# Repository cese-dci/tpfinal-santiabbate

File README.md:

# TP final de la materia Diseño de Circuitos Impresos - CESE - 2020A
## Réplica  modificada Heltec Wifi LoRA V2

Propuesta general: Eliminar el display OLED y reemplazar los circuitos integrados ESP32 y SX1278 por los módulos ESP32-WROOM y Ra-01.

## Resultado

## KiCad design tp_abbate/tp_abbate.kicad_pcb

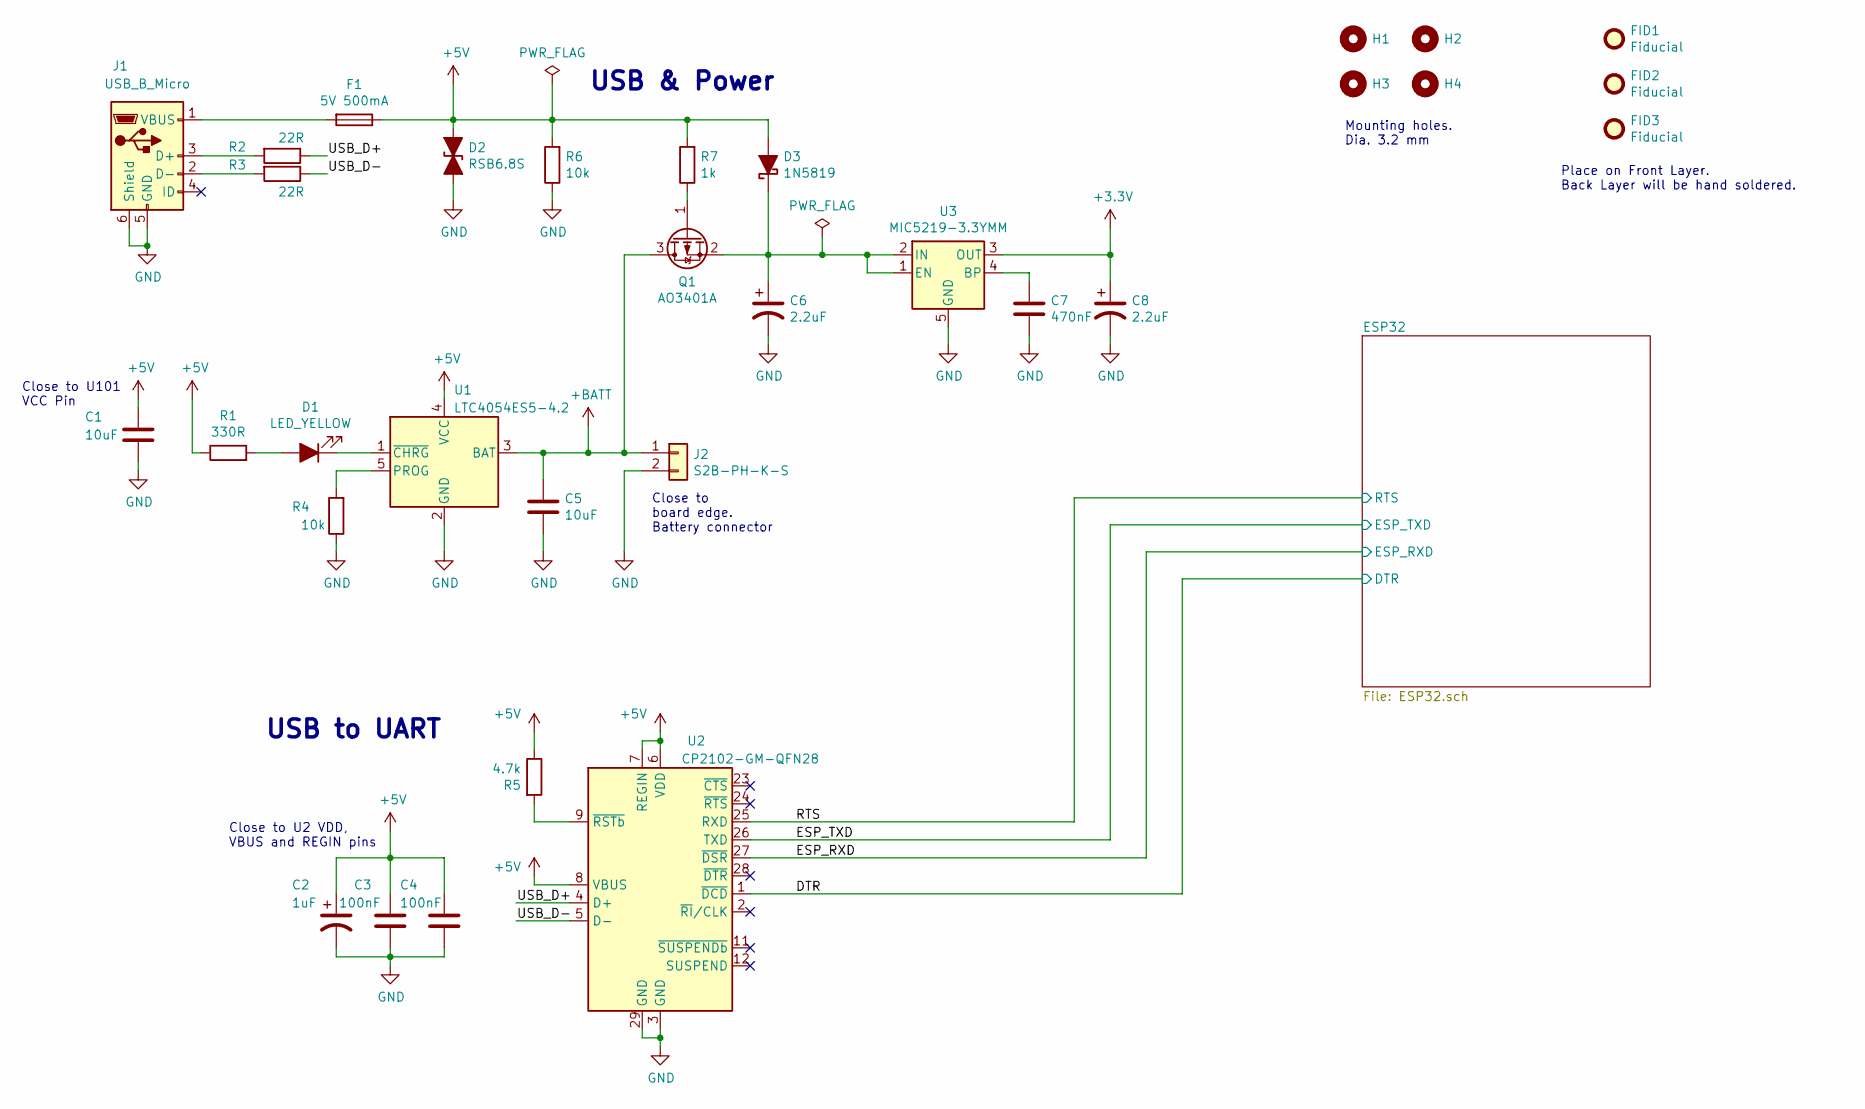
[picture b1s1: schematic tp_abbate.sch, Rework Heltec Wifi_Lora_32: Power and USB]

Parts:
C1, C5: 10uF; CP_EIA-2012-12_Kemet-R_Pad1.30x1.05mm_HandSolder; Digikey# 478-F981C106MSUAJ6CT-ND
C2: 1uF; CP_EIA-3216-10_Kemet-I_Pad1.58x1.35mm_HandSolder; Digikey# 511-TCA1E105M8RCT-ND
C3, C4: 100nF; C_0805_2012Metric_Pad1.15x1.40mm_HandSolder; Digikey# 399-1177-1-ND
C6, C8: 2.2uF; CP_EIA-3216-18_Kemet-A_Pad1.58x1.35mm_HandSolder; Digikey# TAJA225M010SNJ
C7: 470nF; C_0805_2012Metric_Pad1.15x1.40mm_HandSolder; Digikey# 311-4355-1-ND
D1: LED_YELLOW; LED_0805_2012Metric_Pad1.15x1.40mm_HandSolder
D2: RSB6.8S; D_SOD-523; Digikey# RSB6.8STE61TR-ND
D3: 1N5819; D_SOD-123; Digikey# 1N5819HW-FDICT-ND
F1: 5V 500mA; Fuse_0603_1608Metric_Pad1.05x0.95mm_HandSolder; Digikey# F12131CT-ND
FID1, FID2, FID3: Fiducial; Fiducial_0.5mm_Mask1.5mm
H1, H2, H3, H4: MountingHole; MountingHole_1.8mm_M3
J1: USB_B_Micro; USB_Micro-B_Molex_47346-0001; Digikey# WM17141CT-ND
J2: S2B-PH-K-S; JST_PH_S2B-PH-K_1x02_P2.00mm_Horizontal; Digikey# 455-1719-ND
Q1: AO3401A; SOT-23; Digikey# 785-1001-6-ND
R1: 330R; R_0805_2012Metric_Pad1.15x1.40mm_HandSolder
R2, R3: 22R; R_0805_2012Metric_Pad1.15x1.40mm_HandSolder
R4, R6: 10k; R_0805_2012Metric_Pad1.15x1.40mm_HandSolder
R5: 4.7k; R_0805_2012Metric_Pad1.15x1.40mm_HandSolder
R7: 1k; R_0805_2012Metric_Pad1.15x1.40mm_HandSolder
U1: LTC4054ES5-4.2; TSOT-23-5; Digikey# LTC4054ES5-4.2#TRMPBFTR-ND
U2: CP2102-GM-QFN28; QFN-28-1EP_5x5mm_P0.5mm_EP3.35x3.35mm; Digikey# 336-5890-2-ND
U3: MIC5219-3.3YMM; MSOP-8_3x3mm_P0.65mm; Digikey# MIC5219-3.3YMM-TR-ND

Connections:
+3V3: C8.1, U3.3 (OUT); also elsewhere on the board
+5V: C1.1, C2.1, C3.2, C4.1, D2.1 (A1), D3.2 (A), F1.1, R1.1, R5.1, R6.2, R7.2, U1.4 (VCC), U2.6 (VDD), U2.7 (REGIN), U2.8 (VBUS); also elsewhere on the board
+BATT: C5.1, J2.1, Q1.3 (D), U1.3 (BAT); also elsewhere on the board
/DTR: U2.1 (~DCD); also elsewhere on the board
/ESP_RXD: U2.27 (~DSR); also elsewhere on the board
/ESP_TXD: U2.26 (TXD); also elsewhere on the board
/RTS: U2.25 (RXD); also elsewhere on the board
/USB_D+: R2.1, U2.4 (D+)
/USB_D-: R3.1, U2.5 (D-)
GND: C1.2, C2.2, C3.1, C4.2, C5.2, C6.2, C7.2, C8.2, D2.2 (A2), J1.5 (GND), J1.6 (Shield), J2.2, R4.1, R6.1, U1.2 (GND), U2.3 (GND), U2.29 (GND), U3.5 (GND), U3.6 (GND), U3.7 (GND), U3.8 (GND); also elsewhere on the board
unnamed: C6.1, D3.1 (K), Q1.2 (S), U3.1 (EN), U3.2 (IN)
unnamed: C7.1, U3.4 (BP)
unnamed: D1.1 (K), U1.1 (~CHRG)
unnamed: D1.2 (A), R1.2
unnamed: F1.2, J1.1 (VBUS)
unnamed: J1.2 (D-), R3.2
unnamed: J1.3 (D+), R2.2
unnamed: Q1.1 (G), R7.1
unnamed: R4.2, U1.5 (PROG)
unnamed: R5.2, U2.9 (~RSTb)

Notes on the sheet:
Close to board edge. Battery connector
USB to UART
USB & Power
Close to U101 VCC Pin
Close to U2 VDD, VBUS and REGIN pins
Place on Front Layer. Back Layer will be hand soldered.
Mounting holes. Dia. 3.2 mm

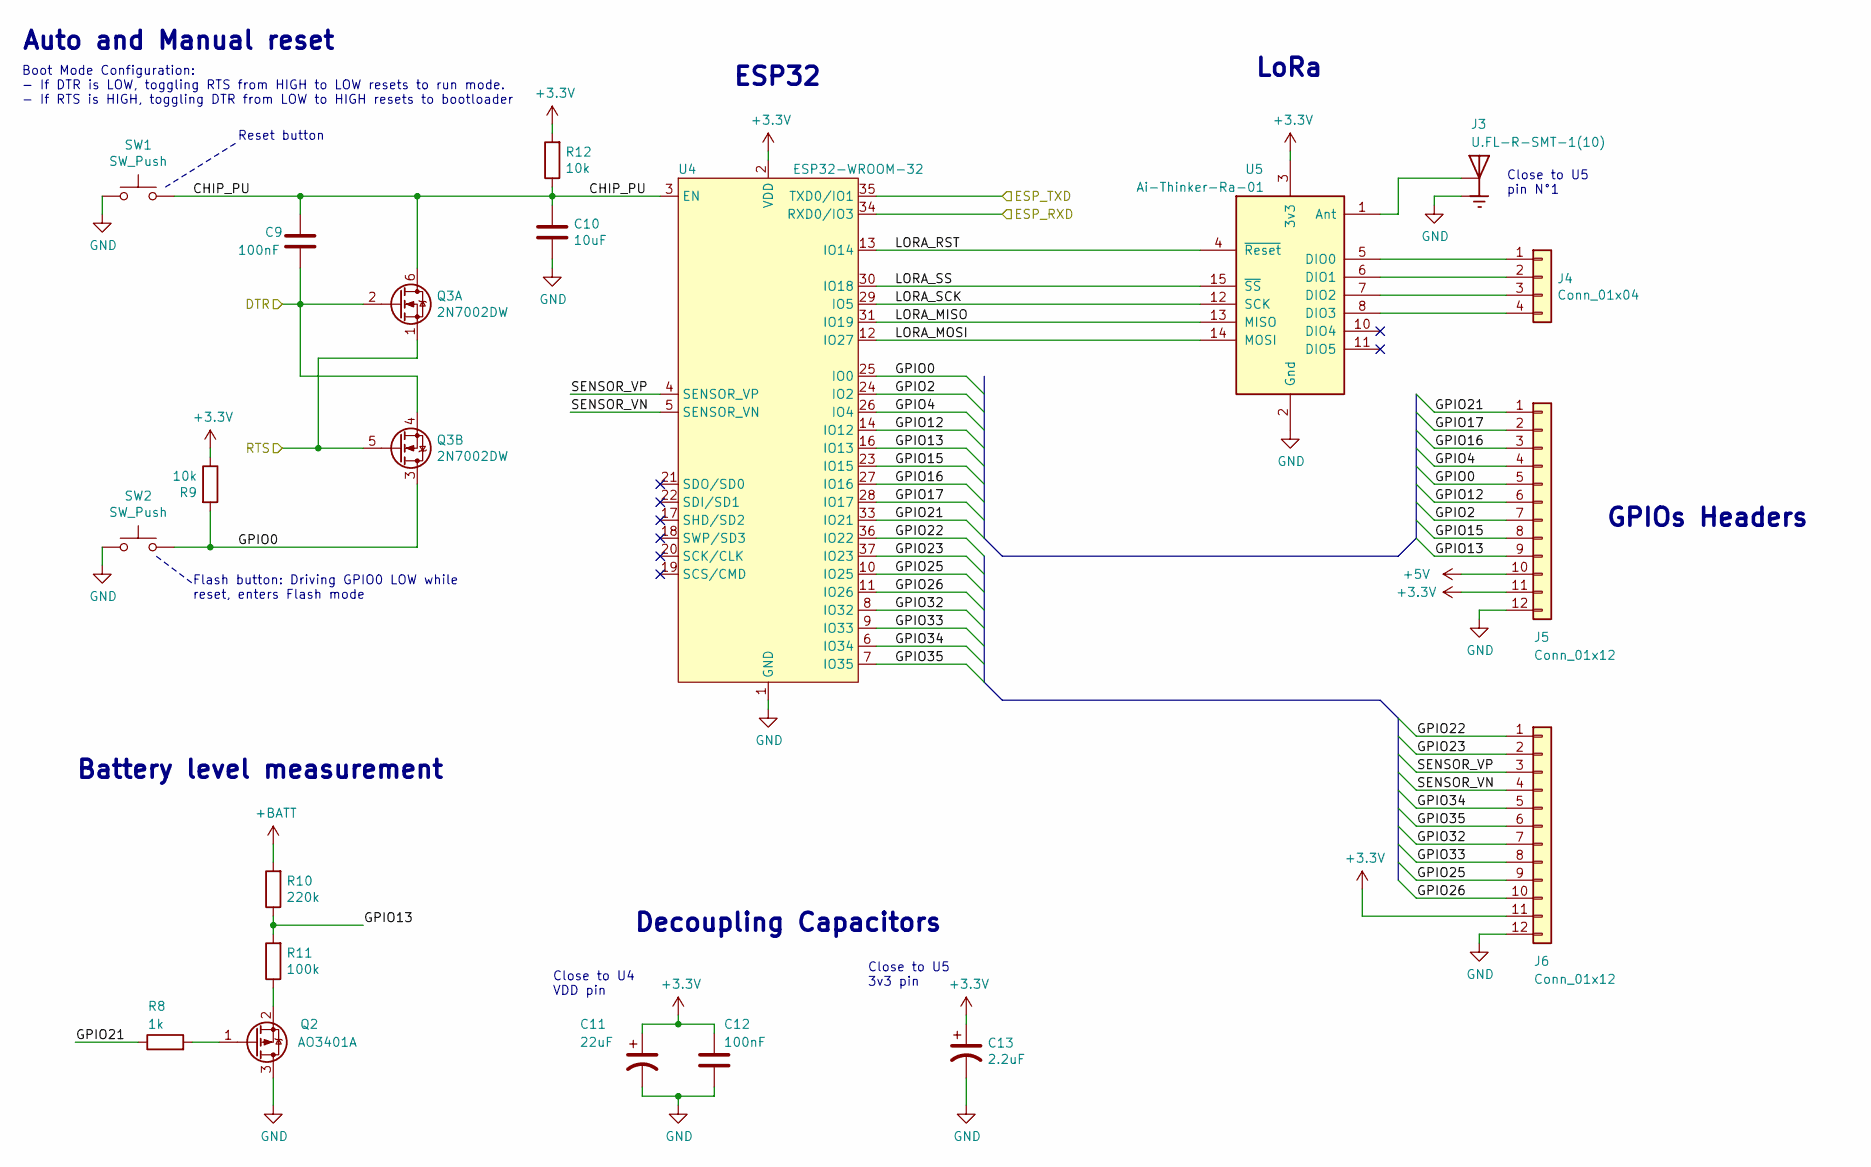
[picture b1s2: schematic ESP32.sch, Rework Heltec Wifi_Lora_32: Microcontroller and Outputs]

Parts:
C9, C12: 100nF; C_0805_2012Metric_Pad1.15x1.40mm_HandSolder; Digikey# 399-1177-1-ND
C10: 10uF; CP_EIA-2012-12_Kemet-R_Pad1.30x1.05mm_HandSolder; Digikey# 478-F981C106MSUAJ6CT-ND
C11: 22uF; CP_EIA-3216-18_Kemet-A_Pad1.58x1.35mm_HandSolder; Digikey# 478-TAJA226K006SNJCT-ND
C13: 2.2uF; CP_EIA-3216-18_Kemet-A_Pad1.58x1.35mm_HandSolder; Digikey# TAJA225M010SNJ
J3: U.FL-R-SMT-1(10); HRS_U.FL-R-SMT-1(10); Digikey# H11891TR-ND
J4: Conn_01x04; PinHeader_1x04_P2.54mm_Vertical
J5, J6: Conn_01x12; PinHeader_1x12_P2.54mm_Vertical
Q2: AO3401A; SOT-23; Digikey# 785-1001-6-ND
Q3: 2N7002DW; SOT-363_SC-70-6_Handsoldering; Digikey# 2N7002DW-FDICT-ND
R8: 1k; R_0805_2012Metric_Pad1.15x1.40mm_HandSolder
R9, R12: 10k; R_0805_2012Metric_Pad1.15x1.40mm_HandSolder
R10: 220k; R_0805_2012Metric_Pad1.15x1.40mm_HandSolder
R11: 100k; R_0805_2012Metric_Pad1.15x1.40mm_HandSolder
SW1, SW2: SW_Push; SW_SPST_CK_RS282G05A3; Digikey# CKN10384CT-ND
U4: ESP32-WROOM-32; Digikey# 1904-1010-1-ND
U5: Ai-Thinker-Ra-01; Ai-Thinker-Ra-01-LoRa

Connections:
+3V3: C11.1, C12.1, C13.1, J5.11, J6.11, R9.1, R12.2, U4.2 (VDD), U5.3 (3v3); also elsewhere on the board
+5V: J5.10; also elsewhere on the board
+BATT: R10.2; also elsewhere on the board
/DTR: C9.2, Q3.2 (G1), Q3.4 (S2); also elsewhere on the board
/ESP32/CHIP_PU: C9.1, C10.1, Q3.6 (D1), R12.1, SW1.2, U4.3 (EN)
/ESP32/GPIO0: J5.5, Q3.3 (D2), R9.2, SW2.2, U4.25 (IO0)
/ESP32/GPIO2: J5.7, U4.24 (IO2)
/ESP32/GPIO4: J5.4, U4.26 (IO4)
/ESP32/GPIO12: J5.6, U4.14 (IO12)
/ESP32/GPIO13: J5.9, R10.1, R11.2, U4.16 (IO13)
/ESP32/GPIO15: J5.8, U4.23 (IO15)
/ESP32/GPIO16: J5.3, U4.27 (IO16)
/ESP32/GPIO17: J5.2, U4.28 (IO17)
/ESP32/GPIO21: J5.1, R8.1, U4.33 (IO21)
/ESP32/GPIO22: J6.1, U4.36 (IO22)
/ESP32/GPIO23: J6.2, U4.37 (IO23)
/ESP32/GPIO25: J6.9, U4.10 (IO25)
/ESP32/GPIO26: J6.10, U4.11 (IO26)
/ESP32/GPIO32: J6.7, U4.8 (IO32)
/ESP32/GPIO33: J6.8, U4.9 (IO33)
/ESP32/GPIO34: J6.5, U4.6 (IO34)
/ESP32/GPIO35: J6.6, U4.7 (IO35)
/ESP32/LORA_MISO: U4.31 (IO19), U5.13 (MISO)
/ESP32/LORA_MOSI: U4.12 (IO27), U5.14 (MOSI)
/ESP32/LORA_RST: U4.13 (IO14), U5.4 (~Reset)
/ESP32/LORA_SCK: U4.29 (IO5), U5.12 (SCK)
/ESP32/LORA_SS: U4.30 (IO18), U5.15 (~SS)
/ESP32/SENSOR_VN: J6.4, U4.5 (SENSOR_VN)
/ESP32/SENSOR_VP: J6.3, U4.4 (SENSOR_VP)
/ESP_RXD: U4.34 (RXD0/IO3); also elsewhere on the board
/ESP_TXD: U4.35 (TXD0/IO1); also elsewhere on the board
/RTS: Q3.1 (S1), Q3.5 (G2); also elsewhere on the board
GND: C10.2, C11.2, C12.2, C13.2, J3.1 (GND), J3.3 (GND), J5.12, J6.12, Q2.3 (D), SW1.1, SW2.1, U4.1 (GND), U4.15 (GND), U4.38 (GND), U4.39 (GND), U5.2 (Gnd), U5.9 (Gnd), U5.16 (Gnd); also elsewhere on the board
unnamed: J3.2 (SIG), U5.1 (Ant)
unnamed: J4.1, U5.5 (DIO0)
unnamed: J4.2, U5.6 (DIO1)
unnamed: J4.3, U5.7 (DIO2)
unnamed: J4.4, U5.8 (DIO3)
unnamed: Q2.1 (G), R8.2
unnamed: Q2.2 (S), R11.1

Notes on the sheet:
ESP32
Close to U4 VDD pin
GPIOs Headers
LoRa
Close to U5 3v3 pin
Flash button: Driving GPIO0 LOW while reset, enters Flash mode
Reset button
Auto and Manual reset
Boot Mode Configuration: - If DTR is LOW, toggling RTS from HIGH to LOW resets to run mode. - If RTS is HIGH, toggling DTR from LOW to HIGH resets to bootloader
Decoupling Capacitors
Battery level measurement
Close to U5 pin N°1

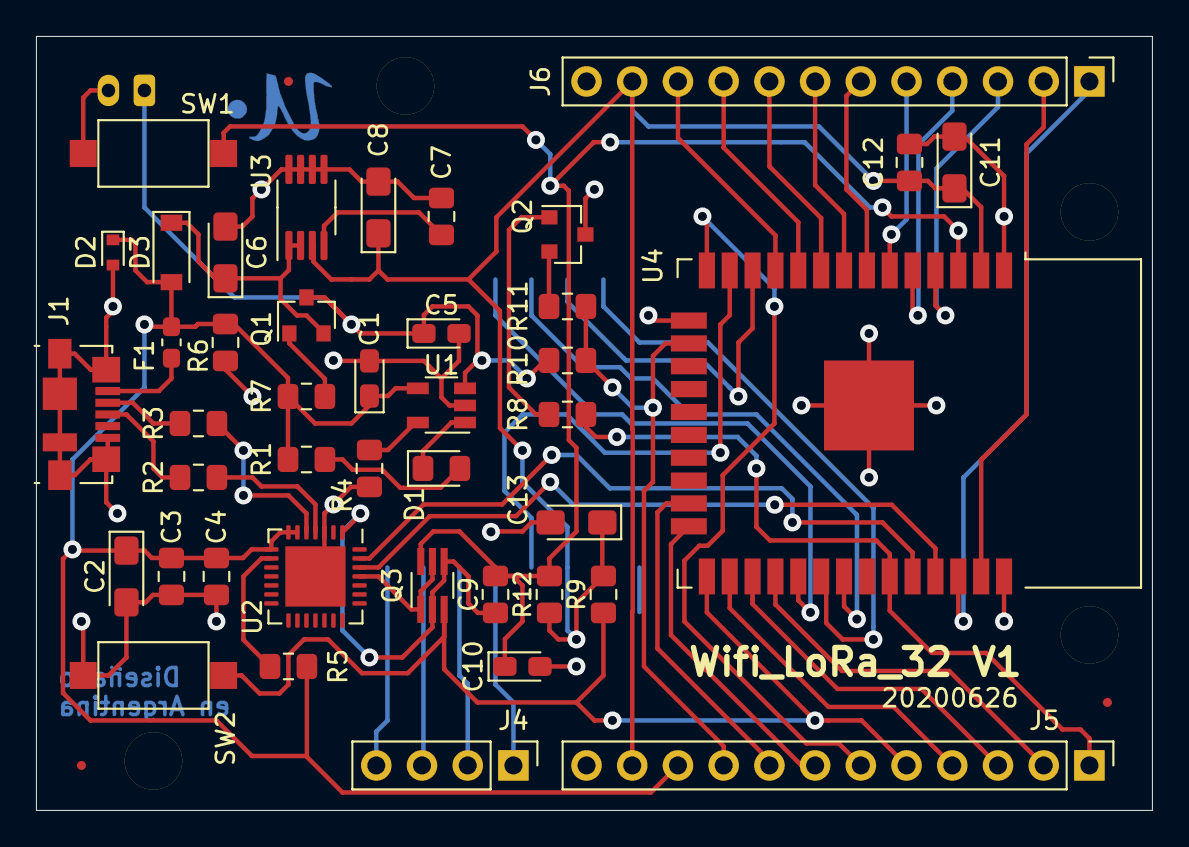
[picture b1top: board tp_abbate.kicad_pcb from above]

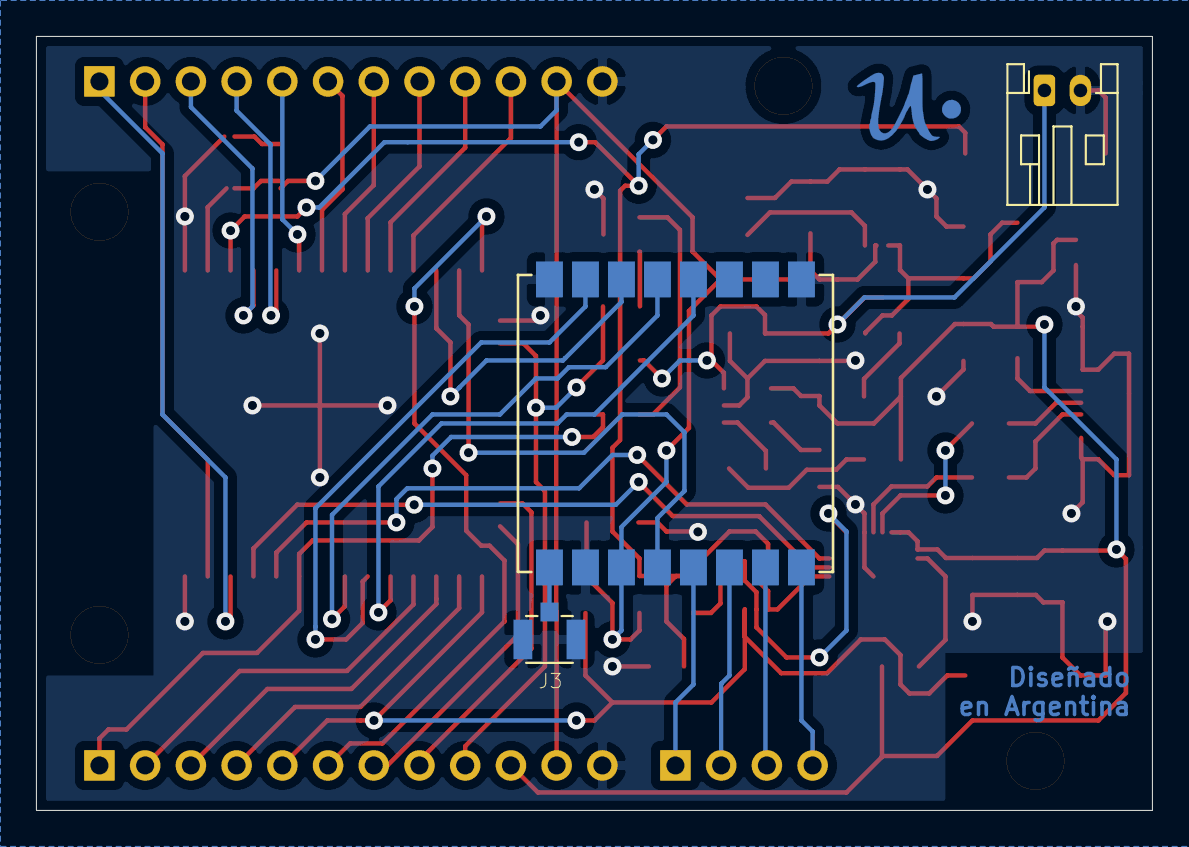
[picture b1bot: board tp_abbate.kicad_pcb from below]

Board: 2 copper layers, 62.0 x 43.0 mm, 52 parts (3 on the bottom side), 52 nets.

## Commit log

2020-06-09 Commit inicial
2020-06-09 Fix comentarios compañero
2020-06-23 Trabajo en PCB - ubicacion de componentes
2020-06-26 WIP revisión PCB
2020-06-26 Subo PCB para revisión compañero
2020-06-27 Corrijo indicaciones de compañero
2020-06-30 Revisión Final - Entrega

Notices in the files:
tp_abbate/ESP32.sch:
Licencia CC-BY 4.0
